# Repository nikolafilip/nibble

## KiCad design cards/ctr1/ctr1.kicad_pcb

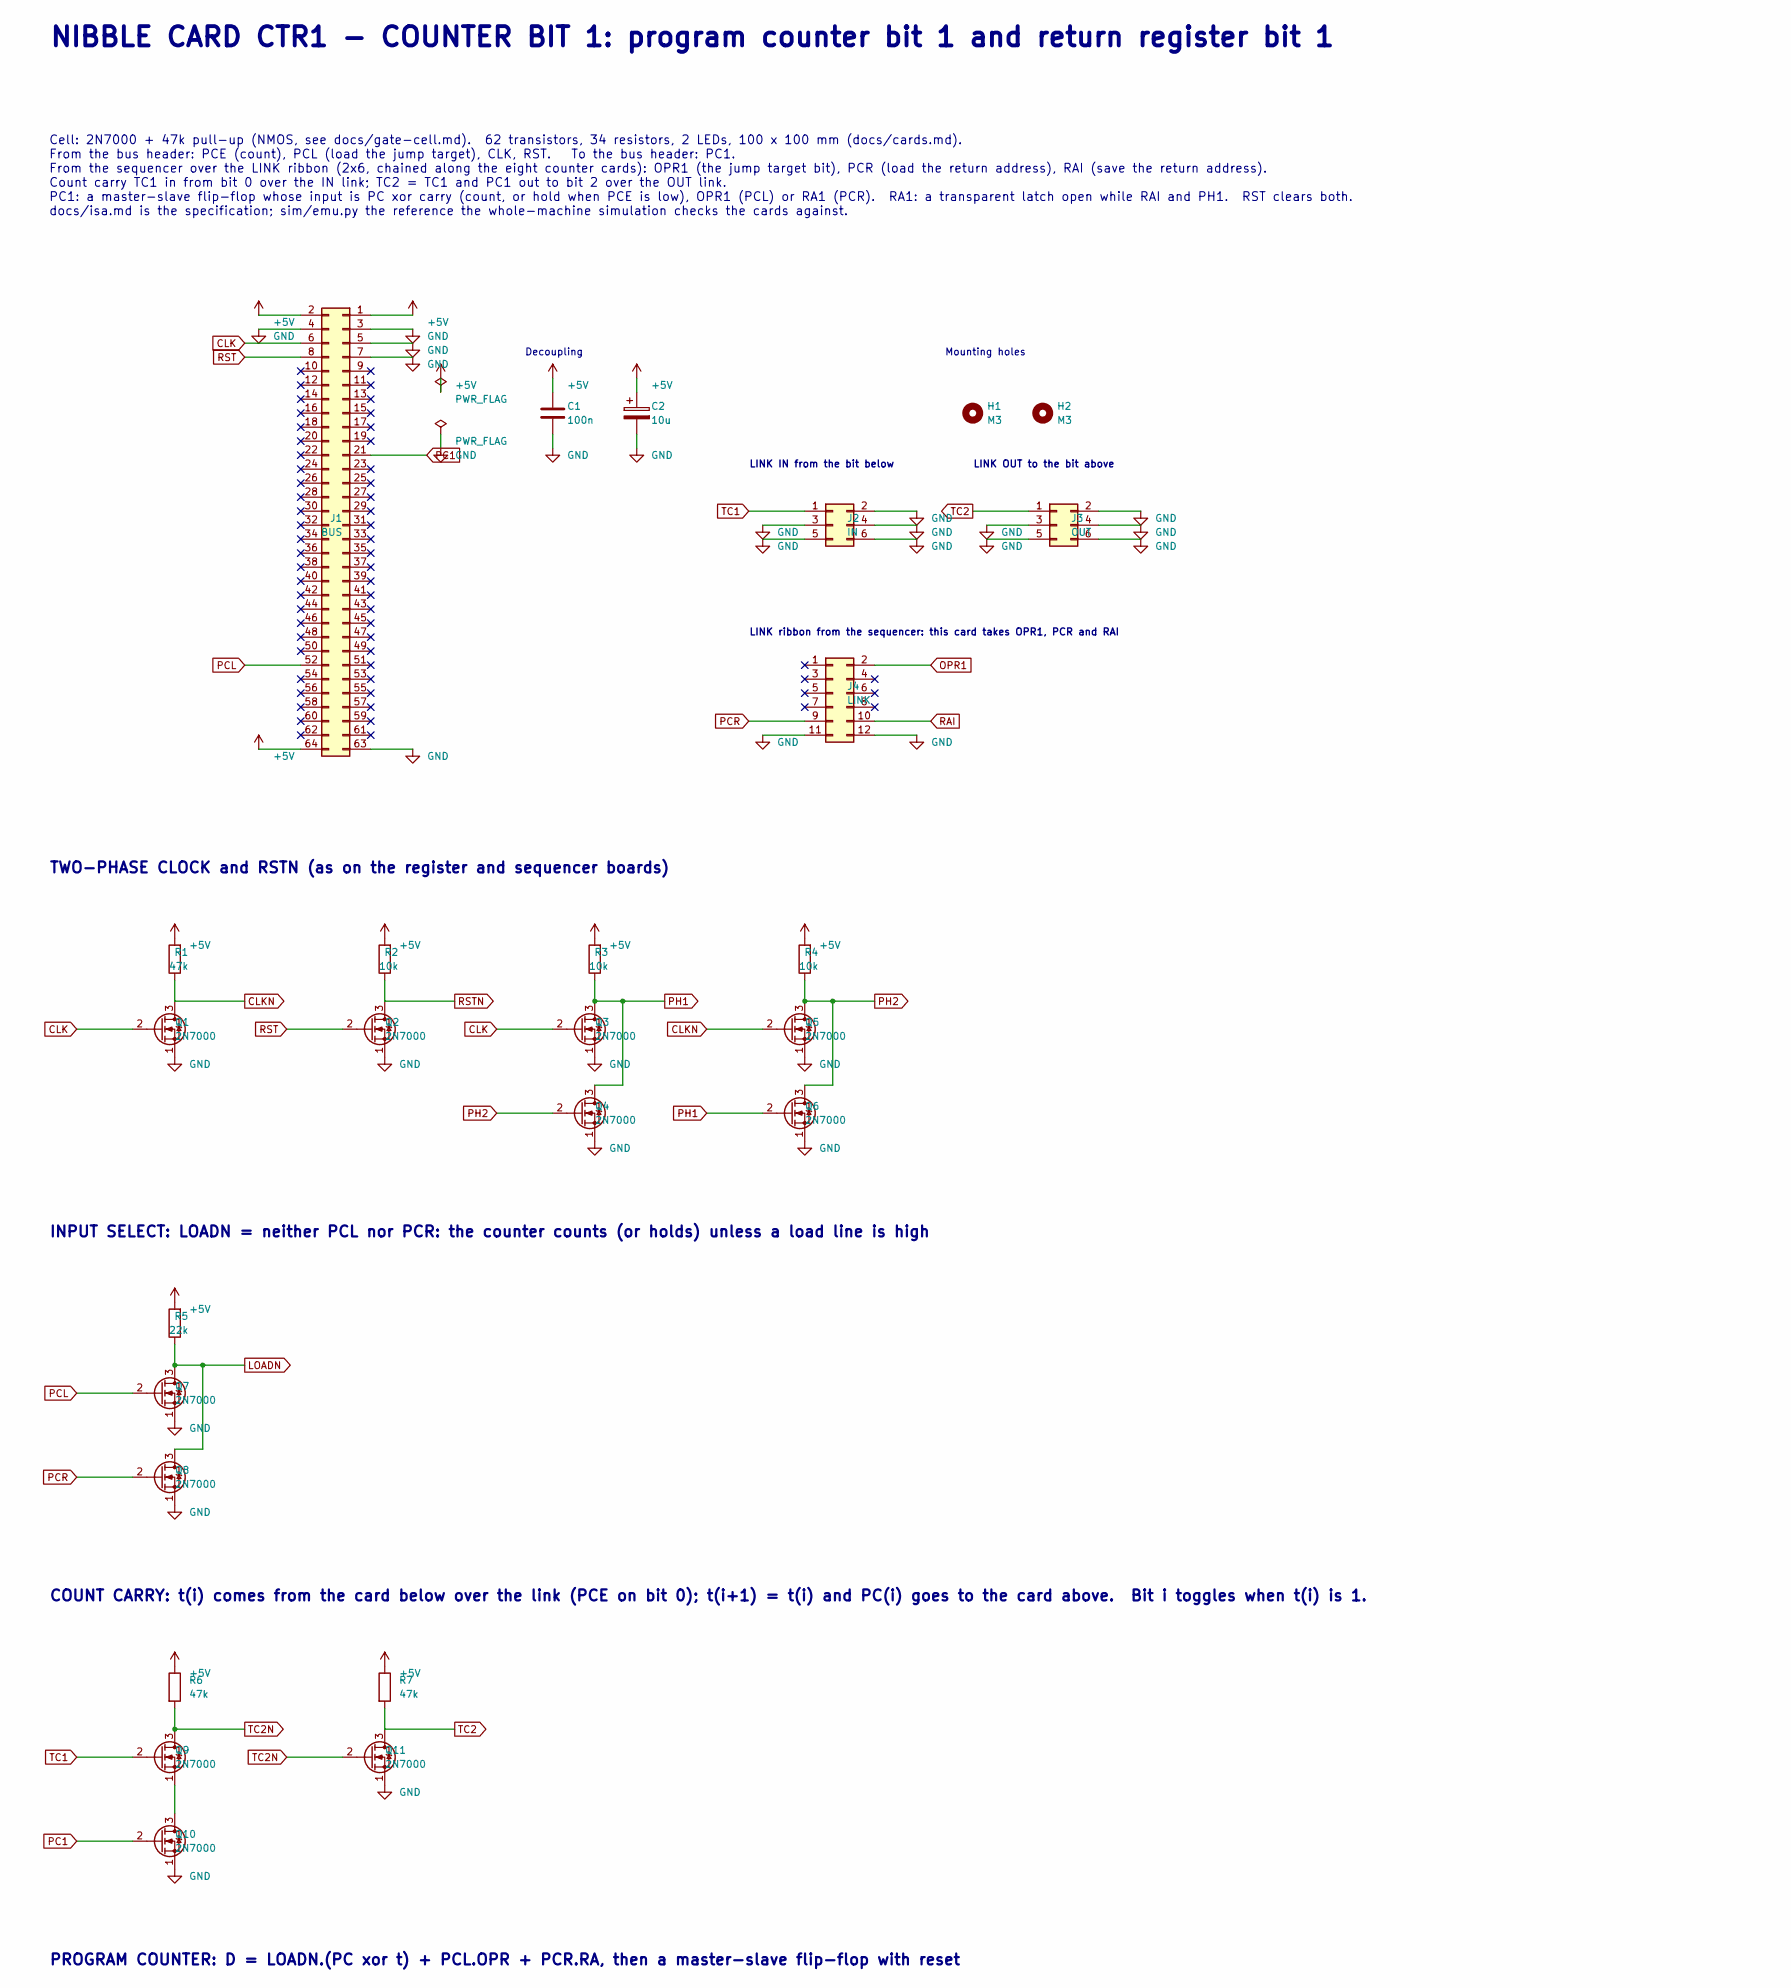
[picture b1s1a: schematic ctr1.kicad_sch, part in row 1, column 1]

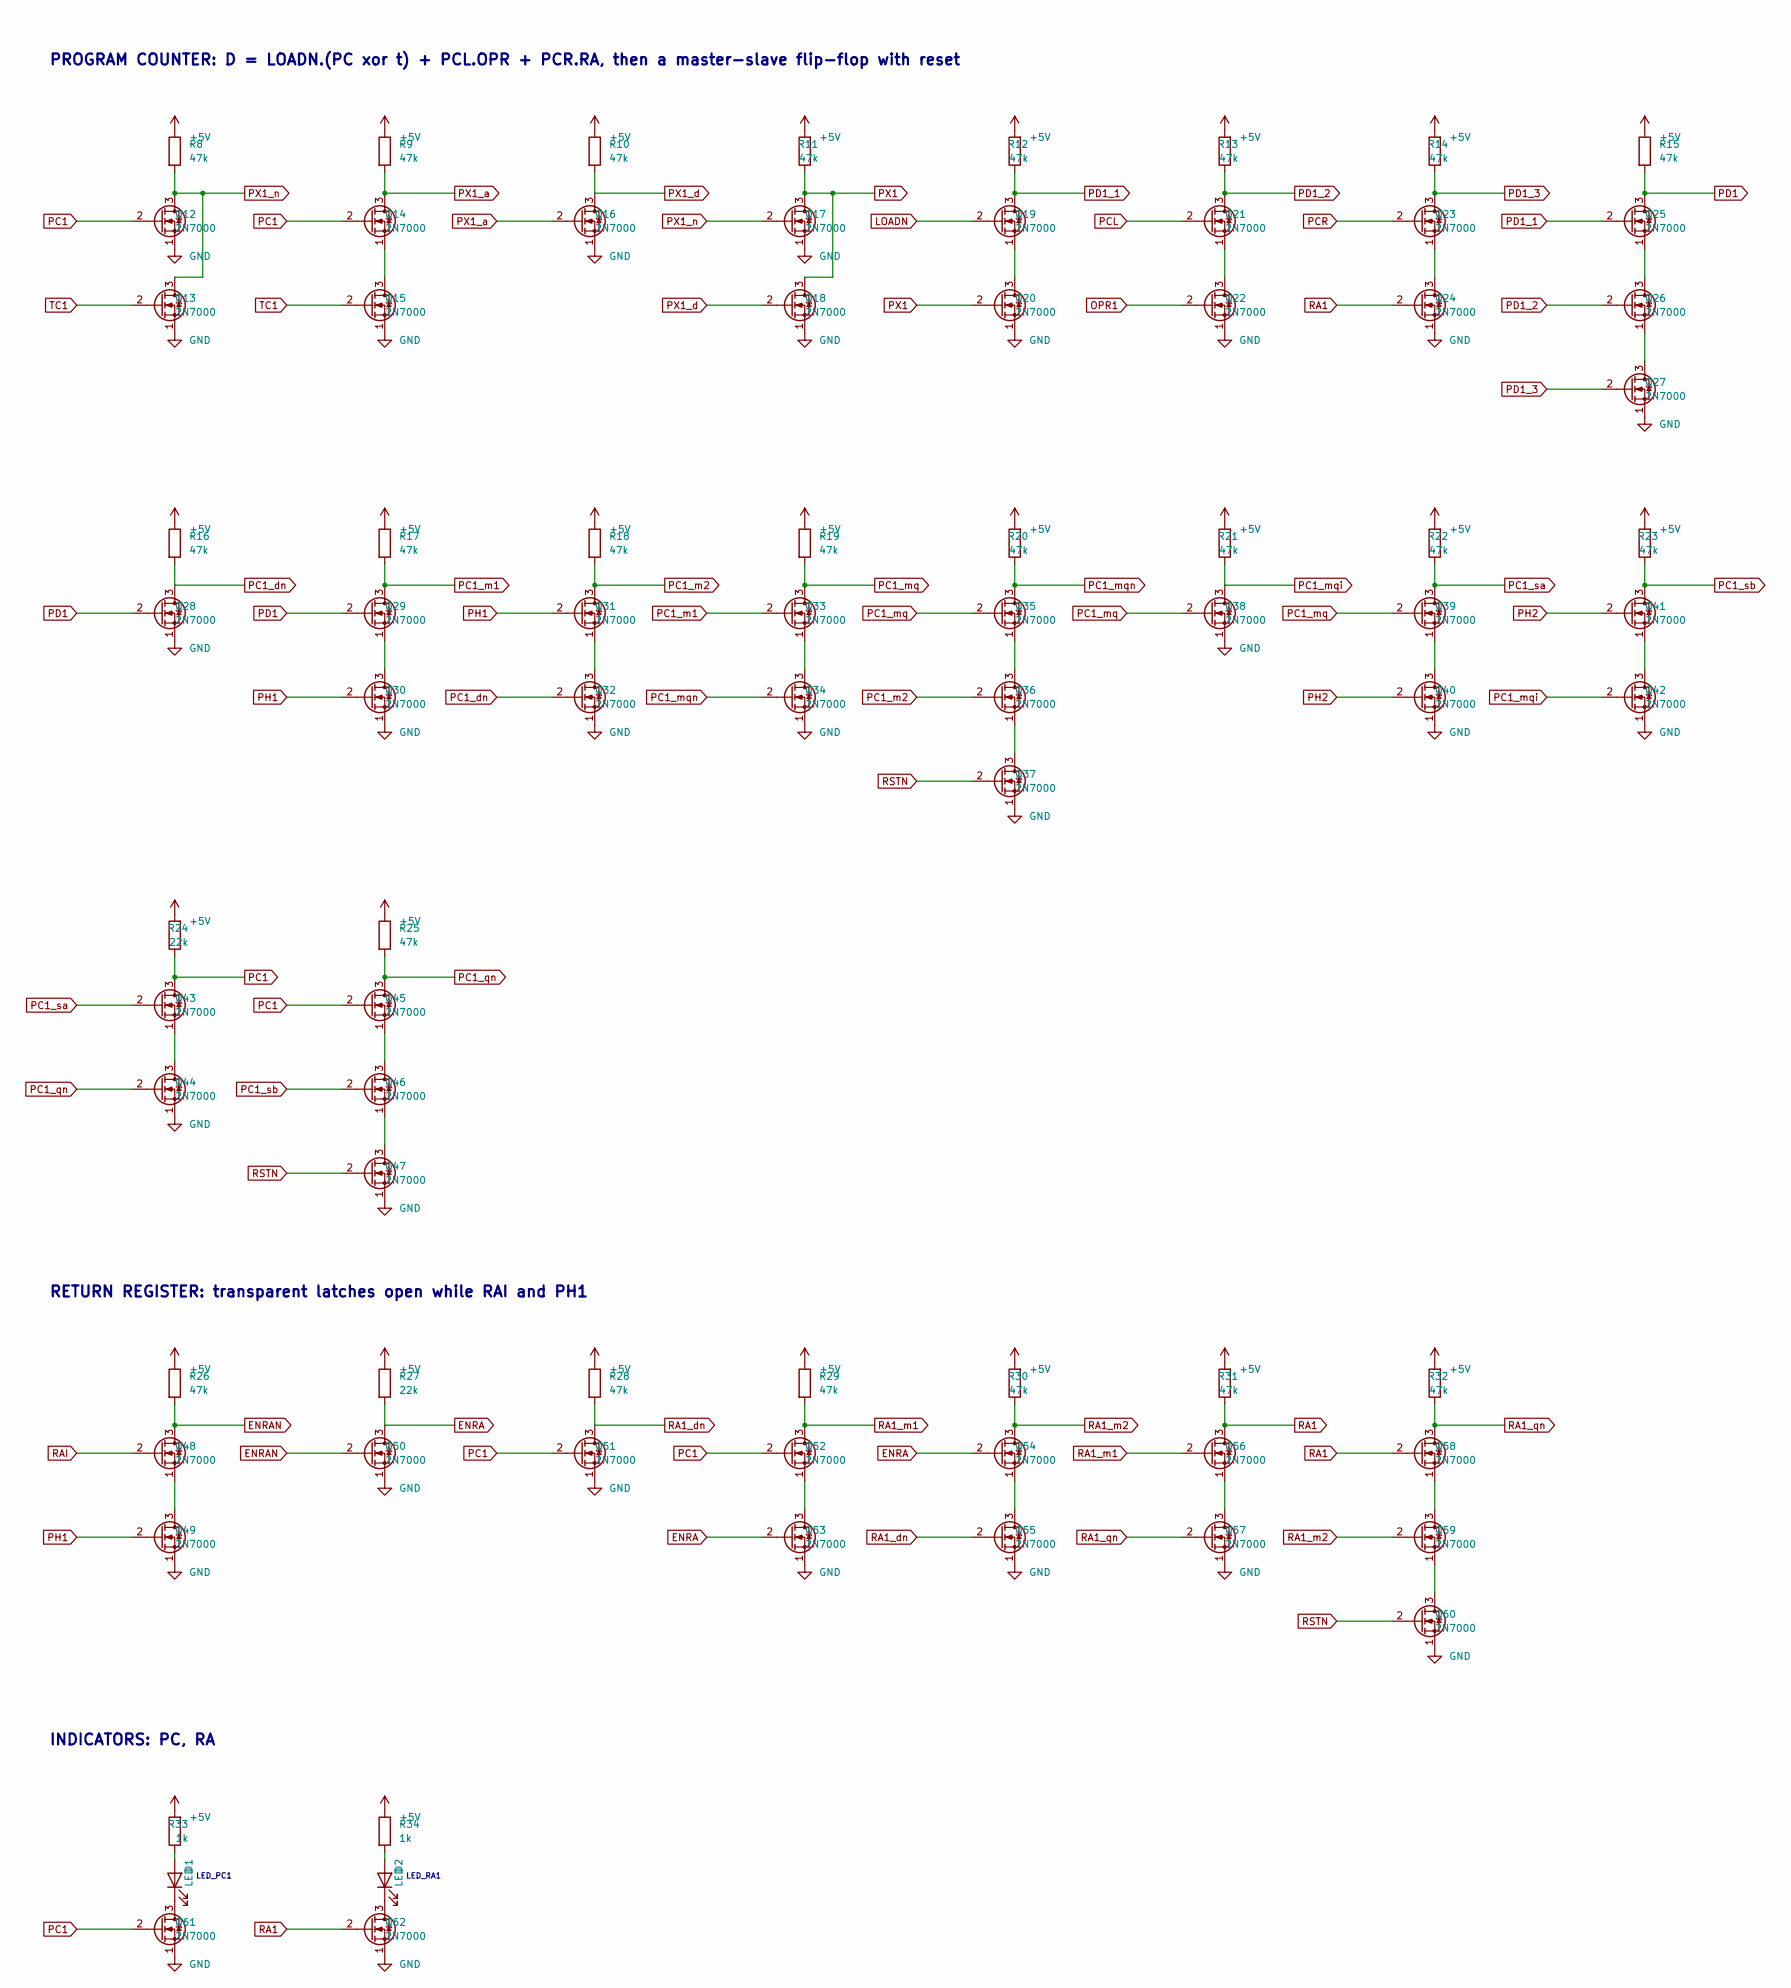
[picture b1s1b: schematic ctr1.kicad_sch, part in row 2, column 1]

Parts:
C1: 100n; C_Disc_D5.0mm_W2.5mm_P2.50mm
C2: 10u; CP_Radial_D5.0mm_P2.00mm
D1, D2: LED; LED_D3.0mm
H1, H2: M3; MountingHole_3.2mm_M3_Pad
J1: BUS; IDC-Header_2x32_P2.54mm_Vertical
J2: IN; IDC-Header_2x03_P2.54mm_Vertical
J3: OUT; IDC-Header_2x03_P2.54mm_Vertical
J4: LINK; IDC-Header_2x06_P2.54mm_Vertical
Q1, Q2, Q3, Q4, Q5, Q6, Q7, Q8, Q9, Q10, Q11, Q12, Q13, Q14, Q15, Q16, Q17, Q18, Q19, Q20, Q21, Q22, Q23, Q24, Q25, Q26, Q27, Q28, Q29, Q30, Q31, Q32, Q33, Q34, Q35, Q36, Q37, Q38, Q39, Q40, Q41, Q42, Q43, Q44, Q45, Q46, Q47, Q48, Q49, Q50, Q51, Q52, Q53, Q54, Q55, Q56, Q57, Q58, Q59, Q60, Q61, Q62: 2N7000; TO-92_Inline_Wide
R1, R6, R7, R8, R9, R10, R11, R12, R13, R14, R15, R16, R17, R18, R19, R20, R21, R22, R23, R25, R26, R28, R29, R30, R31, R32: 47k; R_Axial_DIN0207_L6.3mm_D2.5mm_P5.08mm_Vertical
R2, R3, R4: 10k; R_Axial_DIN0207_L6.3mm_D2.5mm_P5.08mm_Vertical
R5, R24, R27: 22k; R_Axial_DIN0207_L6.3mm_D2.5mm_P5.08mm_Vertical
R33, R34: 1k; R_Axial_DIN0207_L6.3mm_D2.5mm_P5.08mm_Vertical

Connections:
+5V: C1.1, C2.1, J1.1, J1.2, J1.64, R1.2, R2.2, R3.2, R4.2, R5.2, R6.1, R7.1, R8.1, R9.1, R10.1, R11.2, R12.2, R13.2, R14.2, R15.1, R16.1, R17.1, R18.1, R19.1, R20.2, R21.2, R22.2, R23.2, R24.2, R25.1, R26.1, R27.1, R28.1, R29.1, R30.2, R31.2, R32.2, R33.2, R34.1
CLK: J1.6, Q1.2 (G), Q3.2 (G)
CLKN: Q1.3 (D), Q5.2 (G), R1.1
ENRA: Q50.3 (D), Q53.2 (G), Q54.2 (G), R27.2
ENRAN: Q48.3 (D), Q50.2 (G), R26.2
GND: C1.2, C2.2, J1.3, J1.4, J1.5, J1.7, J1.63, J2.2, J2.3, J2.4, J2.5, J2.6, J3.2, J3.3, J3.4, J3.5, J3.6, J4.11, J4.12, Q1.1 (S), Q2.1 (S), Q3.1 (S), Q4.1 (S), Q5.1 (S), Q6.1 (S), Q7.1 (S), Q8.1 (S), Q10.1 (S), Q11.1 (S), Q12.1 (S), Q13.1 (S), Q15.1 (S), Q16.1 (S), Q17.1 (S), Q18.1 (S), Q20.1 (S), Q22.1 (S), Q24.1 (S), Q27.1 (S), Q28.1 (S), Q30.1 (S), Q32.1 (S), Q34.1 (S), Q37.1 (S), Q38.1 (S), Q40.1 (S), Q42.1 (S), Q44.1 (S), Q47.1 (S), Q49.1 (S), Q50.1 (S), Q51.1 (S), Q53.1 (S), Q55.1 (S), Q57.1 (S), Q60.1 (S), Q61.1 (S), Q62.1 (S)
LOADN: Q7.3 (D), Q8.3 (D), Q19.2 (G), R5.1
unnamed: D1.2 (A), R33.1
unnamed: D1.1 (K), Q61.3 (D)
unnamed: D2.2 (A), R34.2
unnamed: D2.1 (K), Q62.3 (D)
unnamed: Q9.1 (S), Q10.3 (D)
unnamed: Q14.1 (S), Q15.3 (D)
unnamed: Q19.1 (S), Q20.3 (D)
unnamed: Q21.1 (S), Q22.3 (D)
unnamed: Q23.1 (S), Q24.3 (D)
unnamed: Q25.1 (S), Q26.3 (D)
unnamed: Q26.1 (S), Q27.3 (D)
unnamed: Q29.1 (S), Q30.3 (D)
unnamed: Q31.1 (S), Q32.3 (D)
unnamed: Q33.1 (S), Q34.3 (D)
unnamed: Q35.1 (S), Q36.3 (D)
unnamed: Q36.1 (S), Q37.3 (D)
unnamed: Q39.1 (S), Q40.3 (D)
unnamed: Q41.1 (S), Q42.3 (D)
unnamed: Q43.1 (S), Q44.3 (D)
unnamed: Q45.1 (S), Q46.3 (D)
unnamed: Q46.1 (S), Q47.3 (D)
unnamed: Q48.1 (S), Q49.3 (D)
unnamed: Q52.1 (S), Q53.3 (D)
unnamed: Q54.1 (S), Q55.3 (D)
unnamed: Q56.1 (S), Q57.3 (D)
unnamed: Q58.1 (S), Q59.3 (D)
unnamed: Q59.1 (S), Q60.3 (D)
OPR1: J4.2, Q22.2 (G)
PC1: J1.21, Q10.2 (G), Q12.2 (G), Q14.2 (G), Q43.3 (D), Q45.2 (G), Q51.2 (G), Q52.2 (G), Q61.2 (G), R24.1
PC1_dn: Q28.3 (D), Q32.2 (G), R16.2
PC1_m1: Q29.3 (D), Q33.2 (G), R17.2
PC1_m2: Q31.3 (D), Q36.2 (G), R18.2
PC1_mq: Q33.3 (D), Q35.2 (G), Q38.2 (G), Q39.2 (G), R19.2
PC1_mqi: Q38.3 (D), Q42.2 (G), R21.1
PC1_mqn: Q34.2 (G), Q35.3 (D), R20.1
PC1_qn: Q44.2 (G), Q45.3 (D), R25.2
PC1_sa: Q39.3 (D), Q43.2 (G), R22.1
PC1_sb: Q41.3 (D), Q46.2 (G), R23.1
PCL: J1.52, Q7.2 (G), Q21.2 (G)
PCR: J4.9, Q8.2 (G), Q23.2 (G)
PD1: Q25.3 (D), Q28.2 (G), Q29.2 (G), R15.2
PD1_1: Q19.3 (D), Q25.2 (G), R12.1
PD1_2: Q21.3 (D), Q26.2 (G), R13.1
PD1_3: Q23.3 (D), Q27.2 (G), R14.1
PH1: Q3.3 (D), Q4.3 (D), Q6.2 (G), Q30.2 (G), Q31.2 (G), Q49.2 (G), R3.1
PH2: Q4.2 (G), Q5.3 (D), Q6.3 (D), Q40.2 (G), Q41.2 (G), R4.1
PX1: Q17.3 (D), Q18.3 (D), Q20.2 (G), R11.1
PX1_a: Q14.3 (D), Q16.2 (G), R9.2
PX1_d: Q16.3 (D), Q18.2 (G), R10.2
PX1_n: Q12.3 (D), Q13.3 (D), Q17.2 (G), R8.2
RA1: Q24.2 (G), Q56.3 (D), Q58.2 (G), Q62.2 (G), R31.1
RA1_dn: Q51.3 (D), Q55.2 (G), R28.2
RA1_m1: Q52.3 (D), Q56.2 (G), R29.2
RA1_m2: Q54.3 (D), Q59.2 (G), R30.1
RA1_qn: Q57.2 (G), Q58.3 (D), R32.1
RAI: J4.10, Q48.2 (G)
RST: J1.8, Q2.2 (G)
RSTN: Q2.3 (D), Q37.2 (G), Q47.2 (G), Q60.2 (G), R2.1
TC1: J2.1, Q9.2 (G), Q13.2 (G), Q15.2 (G)
TC2: J3.1, Q11.3 (D), R7.2
TC2N: Q9.3 (D), Q11.2 (G), R6.2

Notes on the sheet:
NIBBLE CARD CTR1 - COUNTER BIT 1: program counter bit 1 and return register bit 1
Cell: 2N7000 + 47k pull-up (NMOS, see docs/gate-cell.md). 62 transistors, 34 resistors, 2 LEDs, 100 x 100 mm (docs/cards.md). From the bus header: PCE (count), PCL (load the jump target), CLK, RST. To the bus header: PC1. From the sequencer over the LINK ribbon (2x6, chained along the eight counter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
TWO-PHASE CLOCK and RSTN (as on the register and sequencer boards)
INPUT SELECT: LOADN = neither PCL nor PCR: the counter counts (or holds) unless a load line is high
COUNT CARRY: t(i) comes from the card below over the link (PCE on bit 0); t(i+1) = t(i) and PC(i) goes to the card above. Bit i toggles when t(i) is 1.
PROGRAM COUNTER: D = LOADN.(PC xor t) + PCL.OPR + PCR.RA, then a master-slave flip-flop with reset
RETURN REGISTER: transparent latches open while RAI and PH1
INDICATORS: PC, RA
LED_PC1
LED_RA1
Decoupling
Mounting holes
LINK IN from the bit below
LINK OUT to the bit above
LINK ribbon from the sequencer: this card takes OPR1, PCR and RAI

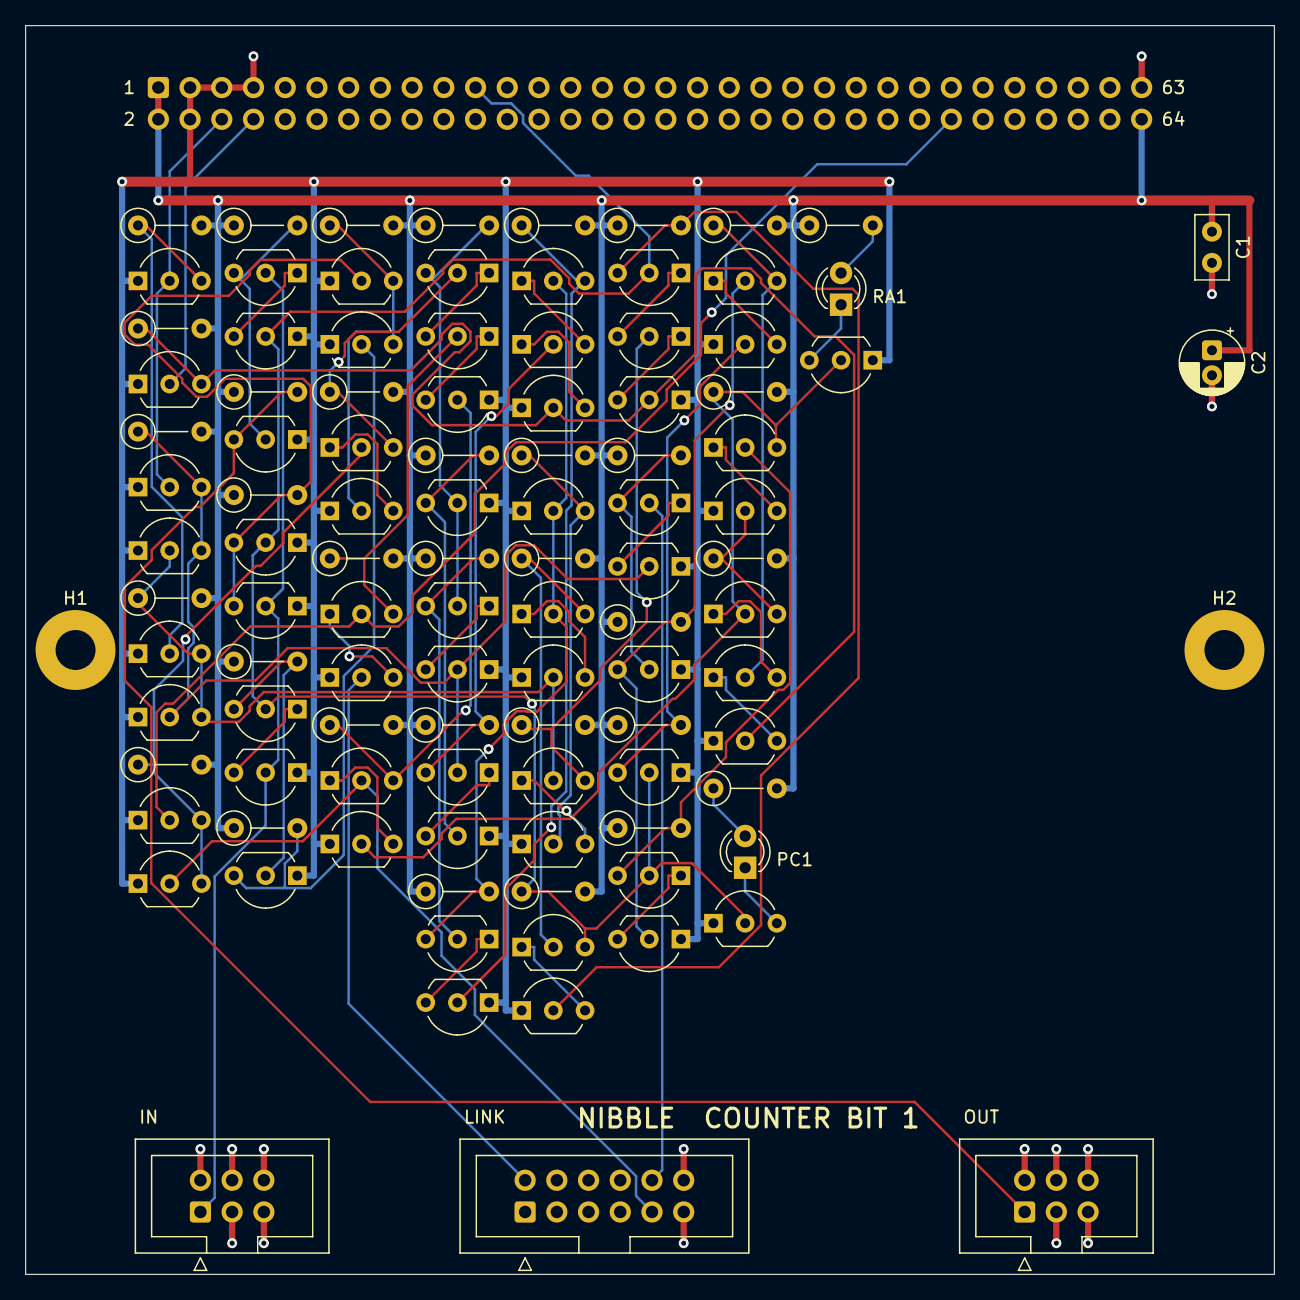
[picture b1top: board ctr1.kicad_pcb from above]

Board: 2 copper layers, 100.0 x 100.0 mm, 106 parts (1 on the bottom side), 68 nets.

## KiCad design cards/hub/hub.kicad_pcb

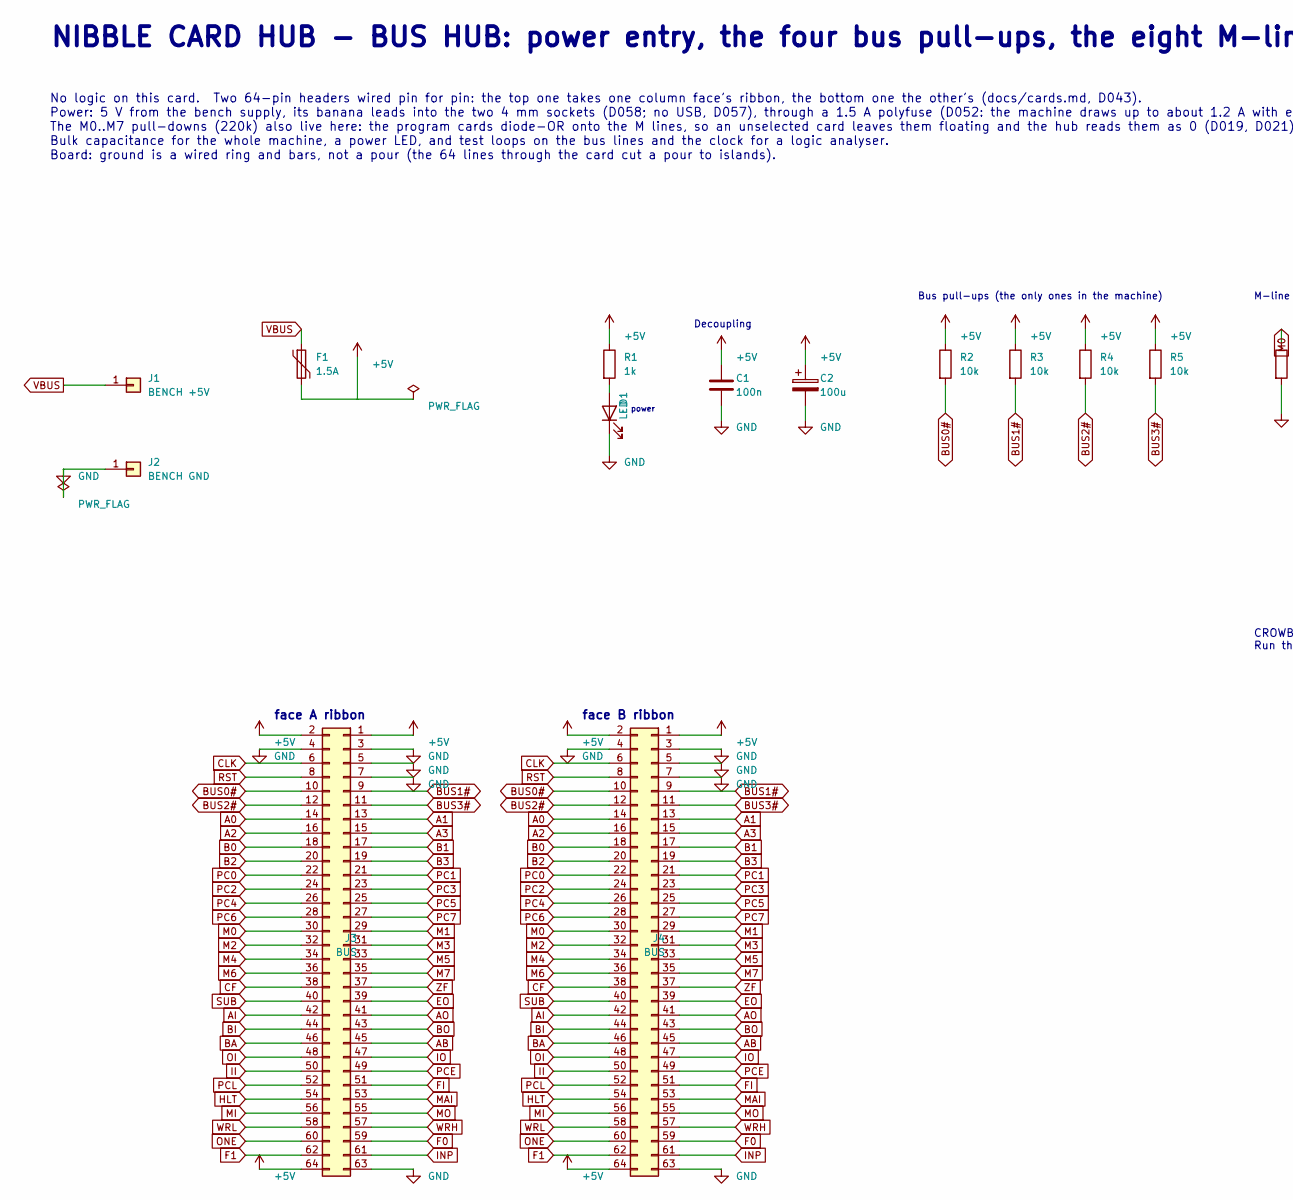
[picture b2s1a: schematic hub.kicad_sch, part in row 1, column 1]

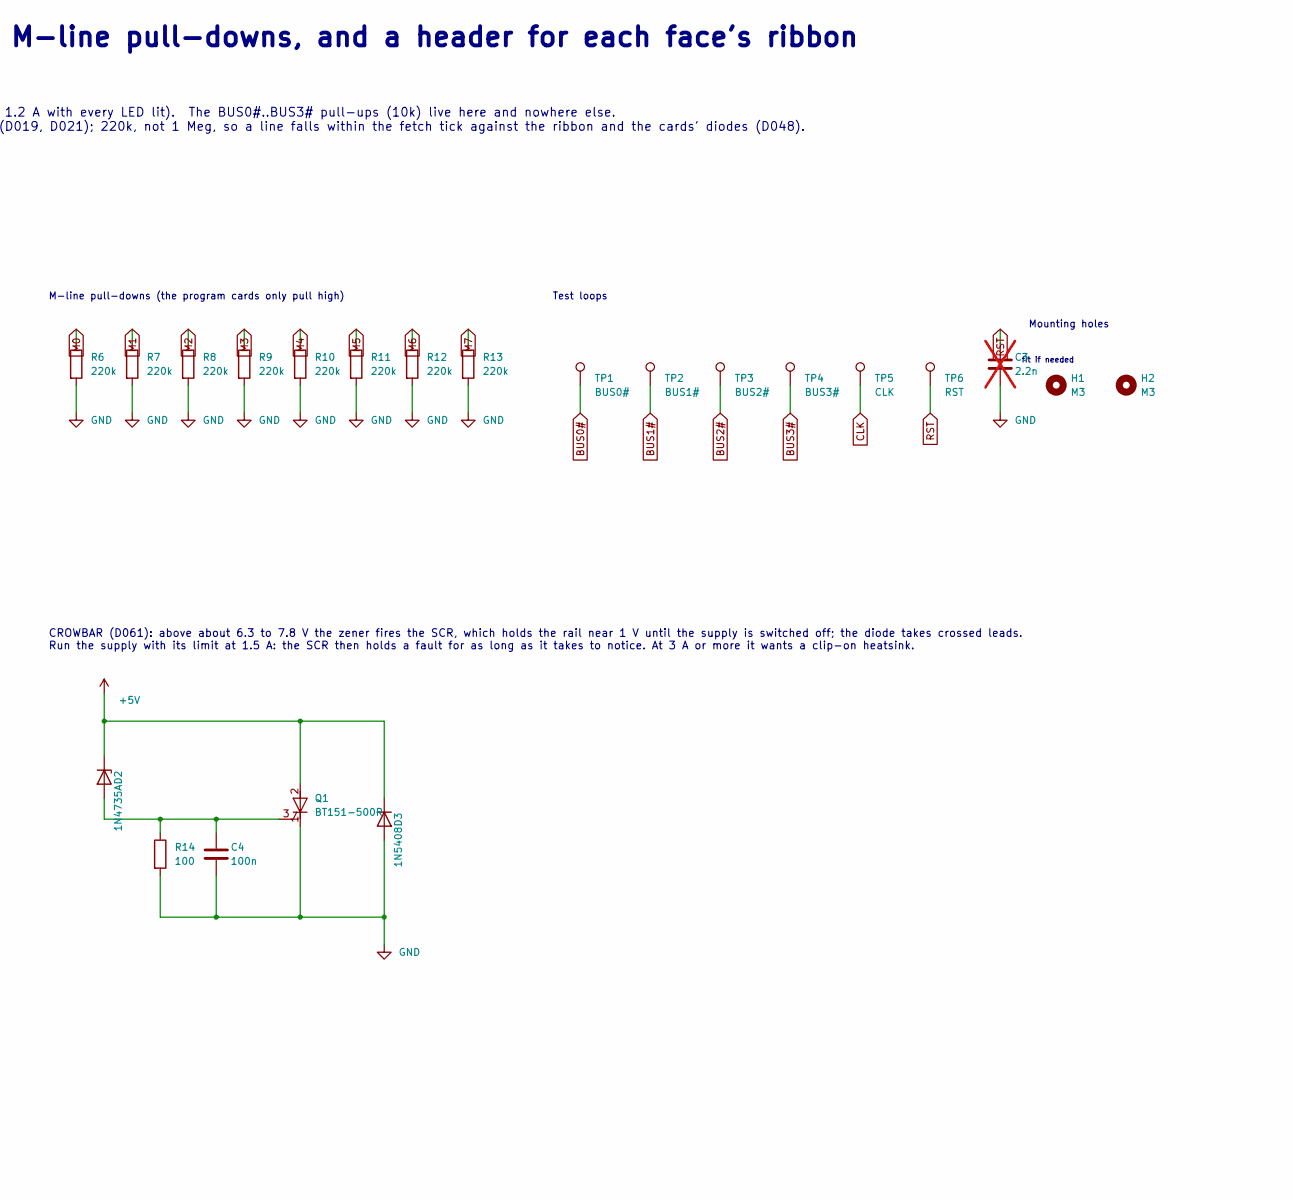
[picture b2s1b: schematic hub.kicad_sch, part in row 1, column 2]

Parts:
C1, C4: 100n; C_Disc_D5.0mm_W2.5mm_P2.50mm
C2: 100u; CP_Radial_D5.0mm_P2.00mm
C3: 2.2n; C_Disc_D5.0mm_W2.5mm_P2.50mm; not fitted
D1: LED; LED_D3.0mm
D2: 1N4735A; D_DO-41_SOD81_P10.16mm_Horizontal
D3: 1N5408; D_DO-201AD_P15.24mm_Horizontal
F1: 1.5A; Fuse_BelFuse_0ZRE0150FF_L23.4mm_W5.3mm
H1, H2: M3; MountingHole_3.2mm_M3_Pad
J1: BENCH +5V; Banana_CalTest_CT3151V1_Vertical
J2: BENCH GND; Banana_CalTest_CT3151V1_Vertical
J3, J4: BUS; IDC-Header_2x32_P2.54mm_Vertical
Q1: BT151-500R; TO-220-3_Vertical
R1: 1k; R_Axial_DIN0207_L6.3mm_D2.5mm_P5.08mm_Vertical
R2, R3, R4, R5: 10k; R_Axial_DIN0207_L6.3mm_D2.5mm_P5.08mm_Vertical
R6, R7, R8, R9, R10, R11, R12, R13: 220k; R_Axial_DIN0207_L6.3mm_D2.5mm_P5.08mm_Vertical
R14: 100; R_Axial_DIN0207_L6.3mm_D2.5mm_P5.08mm_Vertical
TP1: BUS0#; TestPoint_Loop_D2.50mm_Drill1.0mm
TP2: BUS1#; TestPoint_Loop_D2.50mm_Drill1.0mm
TP3: BUS2#; TestPoint_Loop_D2.50mm_Drill1.0mm
TP4: BUS3#; TestPoint_Loop_D2.50mm_Drill1.0mm
TP5: CLK; TestPoint_Loop_D2.50mm_Drill1.0mm
TP6: RST; TestPoint_Loop_D2.50mm_Drill1.0mm

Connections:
+5V: C1.1, C2.1, D2.1 (K), D3.1 (K), F1.2, J3.1, J3.2, J3.64, J4.1, J4.2, J4.64, Q1.2 (A), R1.1, R2.1, R3.1, R4.1, R5.1
A0: J3.14, J4.14
A1: J3.13, J4.13
A2: J3.16, J4.16
A3: J3.15, J4.15
AB: J3.45, J4.45
AI: J3.42, J4.42
AO: J3.41, J4.41
B0: J3.18, J4.18
B1: J3.17, J4.17
B2: J3.20, J4.20
B3: J3.19, J4.19
BA: J3.46, J4.46
BI: J3.44, J4.44
BO: J3.43, J4.43
BUS0#: J3.10, J4.10, R2.2, TP1.1
BUS1#: J3.9, J4.9, R3.2, TP2.1
BUS2#: J3.12, J4.12, R4.2, TP3.1
BUS3#: J3.11, J4.11, R5.2, TP4.1
CF: J3.38, J4.38
CLK: J3.6, J4.6, TP5.1
EO: J3.39, J4.39
F0: J3.59, J4.59
F1: J3.62, J4.62
FI: J3.51, J4.51
GND: C1.2, C2.2, C3.2, C4.2, D1.1 (K), D3.2 (A), J2.1, J3.3, J3.4, J3.5, J3.7, J3.63, J4.3, J4.4, J4.5, J4.7, J4.63, Q1.1 (K), R6.2, R7.2, R8.2, R9.2, R10.2, R11.2, R12.2, R13.2, R14.2
HLT: J3.54, J4.54
II: J3.50, J4.50
INP: J3.61, J4.61
IO: J3.47, J4.47
M0: J3.30, J4.30, R6.1
M1: J3.29, J4.29, R7.1
M2: J3.32, J4.32, R8.1
M3: J3.31, J4.31, R9.1
M4: J3.34, J4.34, R10.1
M5: J3.33, J4.33, R11.1
M6: J3.36, J4.36, R12.1
M7: J3.35, J4.35, R13.1
MAI: J3.53, J4.53
MI: J3.56, J4.56
MO: J3.55, J4.55
unnamed: D1.2 (A), R1.2
unnamed: C4.1, D2.2 (A), Q1.3 (G), R14.1
OI: J3.48, J4.48
ONE: J3.60, J4.60
PC0: J3.22, J4.22
PC1: J3.21, J4.21
PC2: J3.24, J4.24
PC3: J3.23, J4.23
PC4: J3.26, J4.26
PC5: J3.25, J4.25
PC6: J3.28, J4.28
PC7: J3.27, J4.27
PCE: J3.49, J4.49
PCL: J3.52, J4.52
RST: C3.1, J3.8, J4.8, TP6.1
SUB: J3.40, J4.40
VBUS: F1.1, J1.1
WRH: J3.57, J4.57
WRL: J3.58, J4.58
ZF: J3.37, J4.37

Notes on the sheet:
NIBBLE CARD HUB - BUS HUB: power entry, the four bus pull-ups, the eight M-line pull-downs, and a header for each face's ribbon
No logic on this card. Two 64-pin headers wired pin for pin: the top one takes one column face's ribbon, the bottom one the other's (docs/cards.md, D043). Power: 5 V from the bench supply, its banana leads into the two 4 mm sockets (D058; no USB, D057), through a 1.5 A polyfuse (D052: the machine d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
power
Decoupling
Bus pull-ups (the only ones in the machine)
M-line pull-downs (the program cards only pull high)
Test loops
fit if needed
Mounting holes
face A ribbon
face B ribbon
CROWBAR (D061): above about 6.3 to 7.8 V the zener fires the SCR, which holds the rail near 1 V until the supply is switched off; the diode takes crossed leads. Run the supply with its limit at 1.5 A: the SCR then holds a fault for as long as it takes to notice. At 3 A or more it wants a clip-on he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

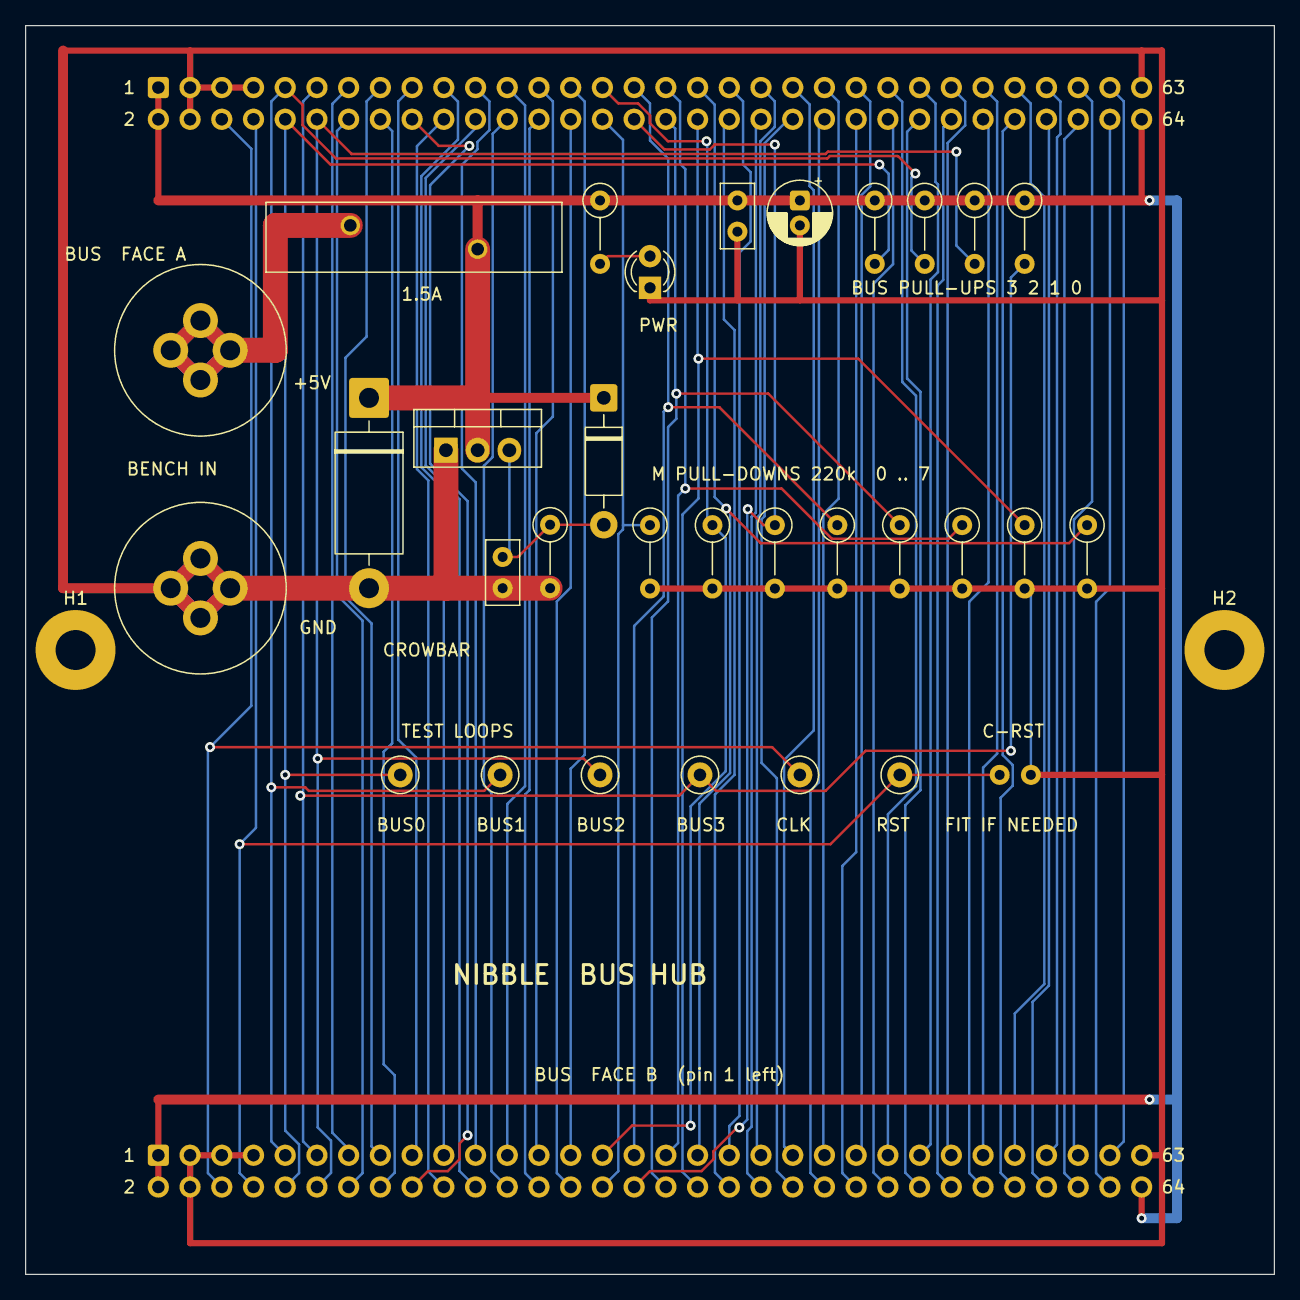
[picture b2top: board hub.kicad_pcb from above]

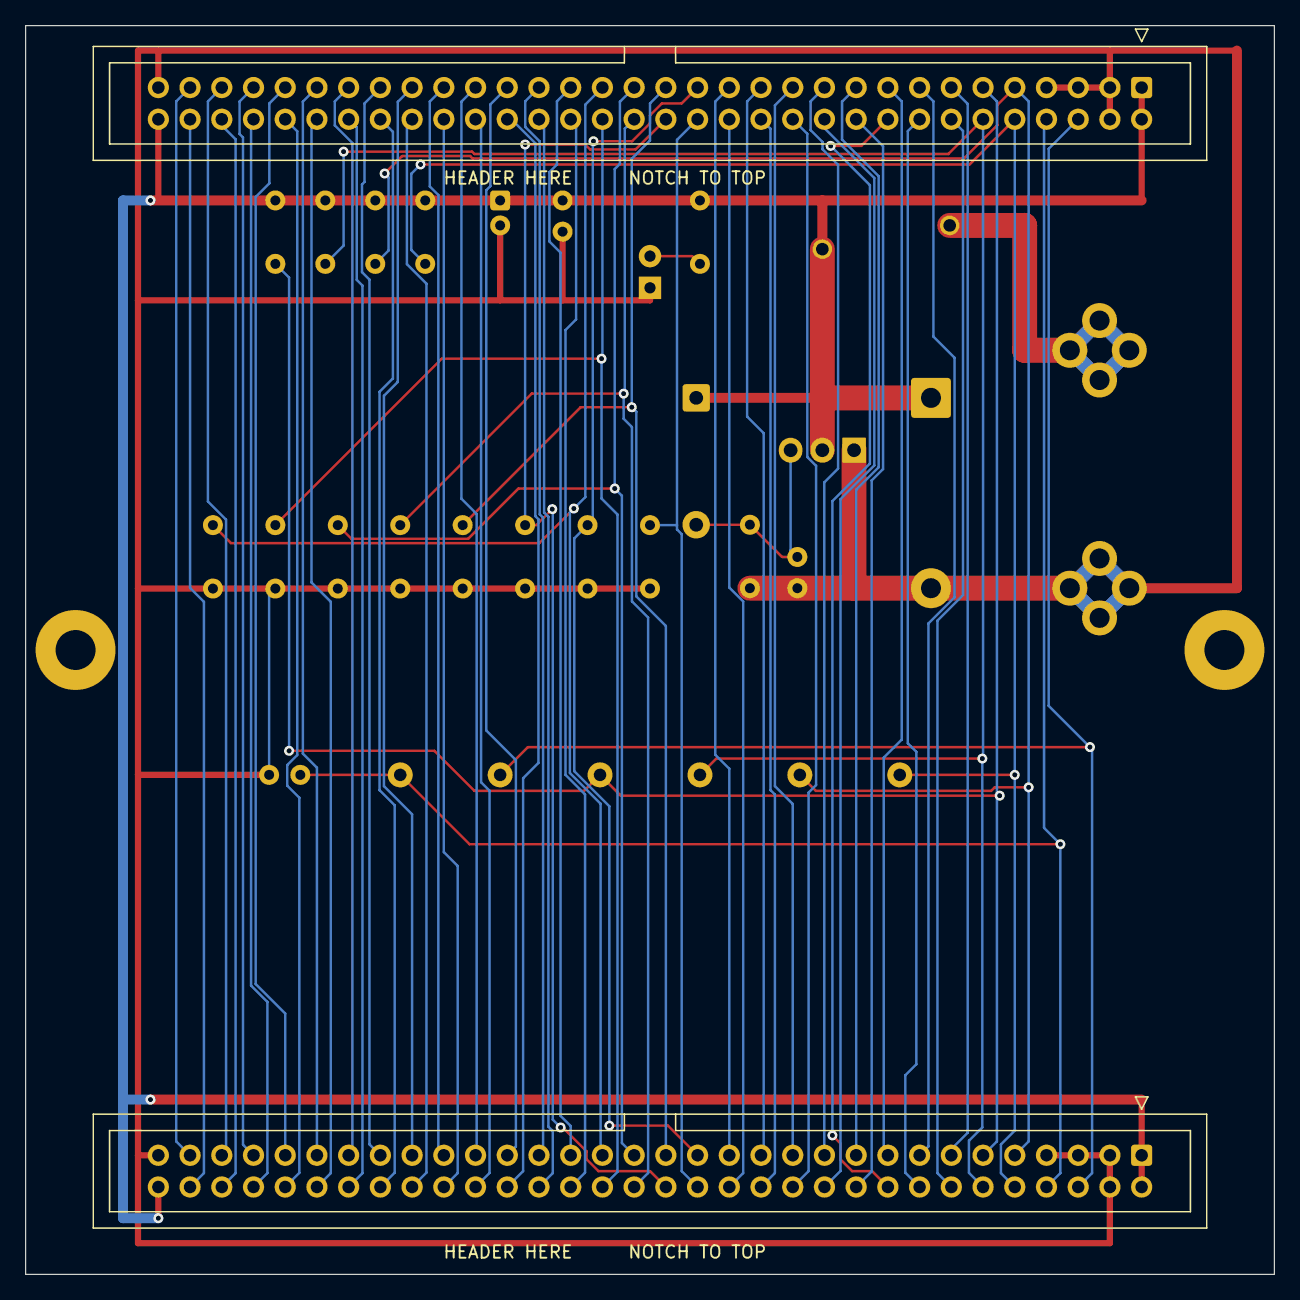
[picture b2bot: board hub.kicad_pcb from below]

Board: 2 copper layers, 100.0 x 100.0 mm, 35 parts (2 on the bottom side), 61 nets.

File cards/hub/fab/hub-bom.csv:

"Reference","Value","Footprint","QUANTITY"
"C1,C4","100n","Capacitor_THT:C_Disc_D5.0mm_W2.5mm_P2.50mm","2"
"C2","100u","Capacitor_THT:CP_Radial_D5.0mm_P2.00mm","1"
"D1","LED","LED_THT:LED_D3.0mm","1"
"D2","1N4735A","Diode_THT:D_DO-41_SOD81_P10.16mm_Horizontal","1"
"D3","1N5408","Diode_THT:D_DO-201AD_P15.24mm_Horizontal","1"
"F1","1.5A","Fuse:Fuse_BelFuse_0ZRE0150FF_L23.4mm_W5.3mm","1"
"J1","BENCH +5V","nibble:Banana_CalTest_CT3151V1_Vertical","1"
"J2","BENCH GND","nibble:Banana_CalTest_CT3151V1_Vertical","1"
"J3,J4","BUS","Connector_IDC:IDC-Header_2x32_P2.54mm_Vertical","2"
"Q1","BT151-500R","Package_TO_SOT_THT:TO-220-3_Vertical","1"
"R1","1k","Resistor_THT:R_Axial_DIN0207_L6.3mm_D2.5mm_P5.08mm_Vertical","1"
"R2-R5","10k","Resistor_THT:R_Axial_DIN0207_L6.3mm_D2.5mm_P5.08mm_Vertical","4"
"R6-R13","220k","Resistor_THT:R_Axial_DIN0207_L6.3mm_D2.5mm_P5.08mm_Vertical","8"
"R14","100","Resistor_THT:R_Axial_DIN0207_L6.3mm_D2.5mm_P5.08mm_Vertical","1"
"TP1","BUS0#","TestPoint:TestPoint_Loop_D2.50mm_Drill1.0mm","1"
"TP2","BUS1#","TestPoint:TestPoint_Loop_D2.50mm_Drill1.0mm","1"
"TP3","BUS2#","TestPoint:TestPoint_Loop_D2.50mm_Drill1.0mm","1"
"TP4","BUS3#","TestPoint:TestPoint_Loop_D2.50mm_Drill1.0mm","1"
"TP5","CLK","TestPoint:TestPoint_Loop_D2.50mm_Drill1.0mm","1"
"TP6","RST","TestPoint:TestPoint_Loop_D2.50mm_Drill1.0mm","1"
